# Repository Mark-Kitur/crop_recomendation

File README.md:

**Smart Crop Recommendation System**

link to the video: https://youtu.be/nVsl1SV6peM?si=QAl62YudmvHhIrHM

**Overview**

This project implements a Crop Recommendation System that suggests the most suitable crop to grow based on soil nutrients and environmental conditions. It combines Machine Learning (ML) with IoT (ESP8266 microcontroller) to support precision agriculture.
The workflow:
Collected and preprocessed agricultural data (soil nutrients & climate).
Trained a Random Forest Classifier model to recommend crops.
 Built a Flask web application for user-friendly crop prediction and farming advice.
 Converted the trained ML model to C code (micromlgen) and deployed it on an ESP8266 NodeMCU microcontroller.

Dataset
The dataset includes soil and environmental features:
N: Nitrogen content ratio in soil
P: Phosphorus content ratio in soil
K: Potassium content ratio in soil
Temperature: in °C
Humidity: in %
pH: Soil acidity/alkalinity
Rainfall: in mm

Tech Stack

Machine Learning: Random Forest Classifier (scikit-learn)

Web Framework: Ruby and Flask

Frontend: HTML, CSS (simple UI for predictions)

Microcontroller: ESP8266 (NodeMCU)

TinyML Library: micromlgen for C model export

Flask Web App
The web app allows users to:
Input soil & environmental parameters.
Get the best crop recommendation.
Receive advice on optimizing conditions (nutrients, pH, rainfall, etc.).

**Ruby Backend With ONNX Runtime**
The second deployment path validates language-agnostic inference by converting the trained Random Forest model to ONNX format.

Key Steps

Export trained model from Python → ONNX

Load ONNX model in Ruby using onnxruntime gem

Run inference directly from Ruby backend code

Serve predictions to a lightweight Ruby-based web endpoint or CLI script

Purpose

Demonstrates cross-platform, cross-language model deployment

Makes the engine compatible with Ruby web stacks (e.g., Rails, Sinatra)

Confirms interoperability without retraining or rewriting ML code

Ruby Deployment Capabilities

The Ruby ONNX version can:

Accept soil parameters via a web form or API

Run fast inference locally using ONNX Runtime

Return the crop recommendation + condition improvement notes

**ESP8266 Deployment**
The trained Random Forest model was converted into C code.
Deployed on ESP8266 NodeMCU with:
DHT11 sensor for temperature & humidity.
LCD display to show predicted crop.
Random values (for testing) simulating N, P, K, pH, rainfall.
Feel free to fork, improve, or suggest enhancements. Together, let’s make farming smarter

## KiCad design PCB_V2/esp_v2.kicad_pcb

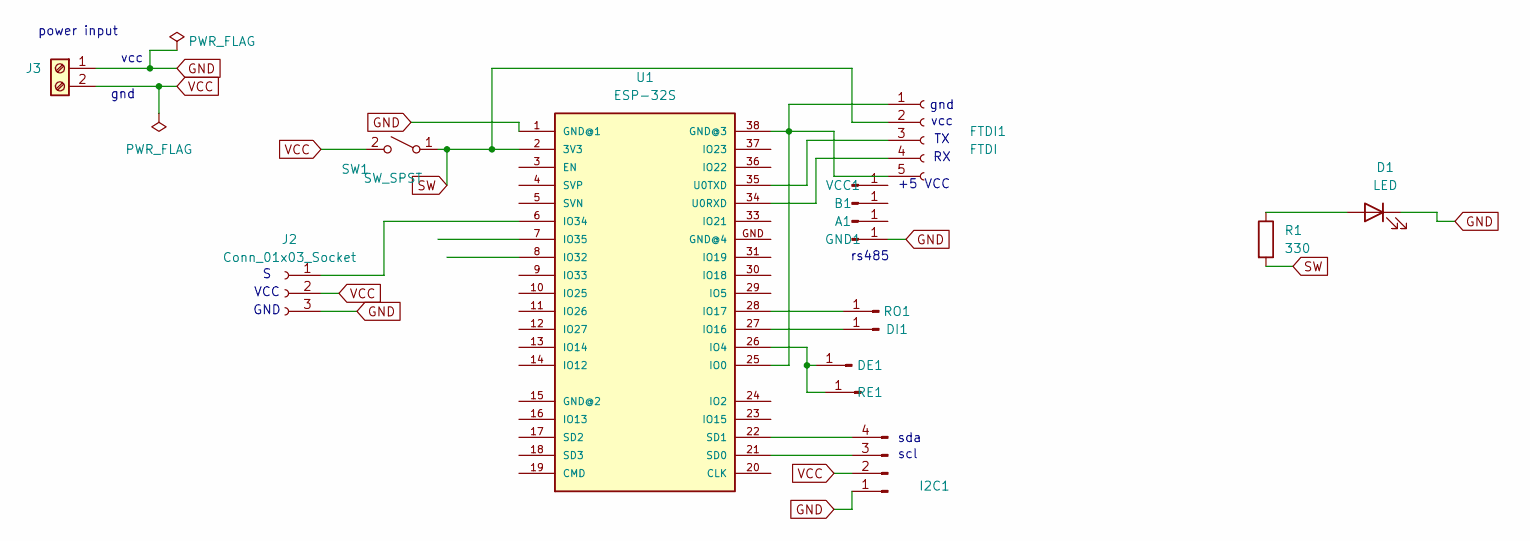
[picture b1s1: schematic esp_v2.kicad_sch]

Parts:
A1: Conn_01x01_Pin; PinHeader_1x01_P2.54mm_Vertical
B1: Conn_01x01_Pin; PinHeader_1x01_P2.54mm_Vertical
D1: LED; LED_D1.8mm_W3.3mm_H2.4mm
DE1: Conn_01x01_Pin; PinHeader_1x01_P2.54mm_Vertical
DI1: DI; PinHeader_1x01_P2.54mm_Vertical
FTDI1: FTDI; PinSocket_1x05_P2.54mm_Vertical
GND1: Conn_01x01_Pin; PinHeader_1x01_P2.54mm_Vertical
I2C1: Conn_01x04_Pin; PinHeader_1x04_P2.54mm_Vertical
J2: Conn_01x03_Socket; PinSocket_1x03_P2.54mm_Vertical
J3: Screw_Terminal_01x02; TerminalBlock_4Ucon_1x02_P3.50mm_Vertical
R1: 330; R_0815_2038Metric_Pad1.20x4.05mm_HandSolder
RE1: Conn_01x01_Pin; PinHeader_1x01_P2.54mm_Vertical
RO1: Conn_01x01_Pin; PinHeader_1x01_P2.54mm_Vertical
SW1: SW_SPST; SW_DIP_SPSTx01_Slide_6.7x4.1mm_W8.61mm_P2.54mm_LowProfile
U1: ESP-32S
VCC1: Conn_01x01_Pin; PinHeader_1x01_P2.54mm_Vertical

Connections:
GND: D1.1 (K), GND1.1, I2C1.1, J2.3, J3.1, U1.1 (GND@1)
unnamed: D1.2 (A), R1.1
unnamed: DE1.1, RE1.1, U1.26 (IO4)
unnamed: DI1.1, U1.27 (IO16)
unnamed: FTDI1.1, FTDI1.5, U1.25 (IO0), U1.38 (GND@3)
unnamed: FTDI1.3, U1.35 (U0TXD)
unnamed: FTDI1.4, U1.34 (U0RXD)
unnamed: I2C1.3, U1.21 (SD0)
unnamed: I2C1.4, U1.22 (SD1)
unnamed: J2.1, U1.6 (IO34)
unnamed: RO1.1, U1.28 (IO17)
SW: FTDI1.2, R1.2, SW1.1 (A), U1.2 (3V3)
VCC: I2C1.2, J2.2, J3.2, SW1.2 (B)

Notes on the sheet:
sda
+5 VCC
VCC
vcc
scl
gnd
power input
gnd
rs485
GND

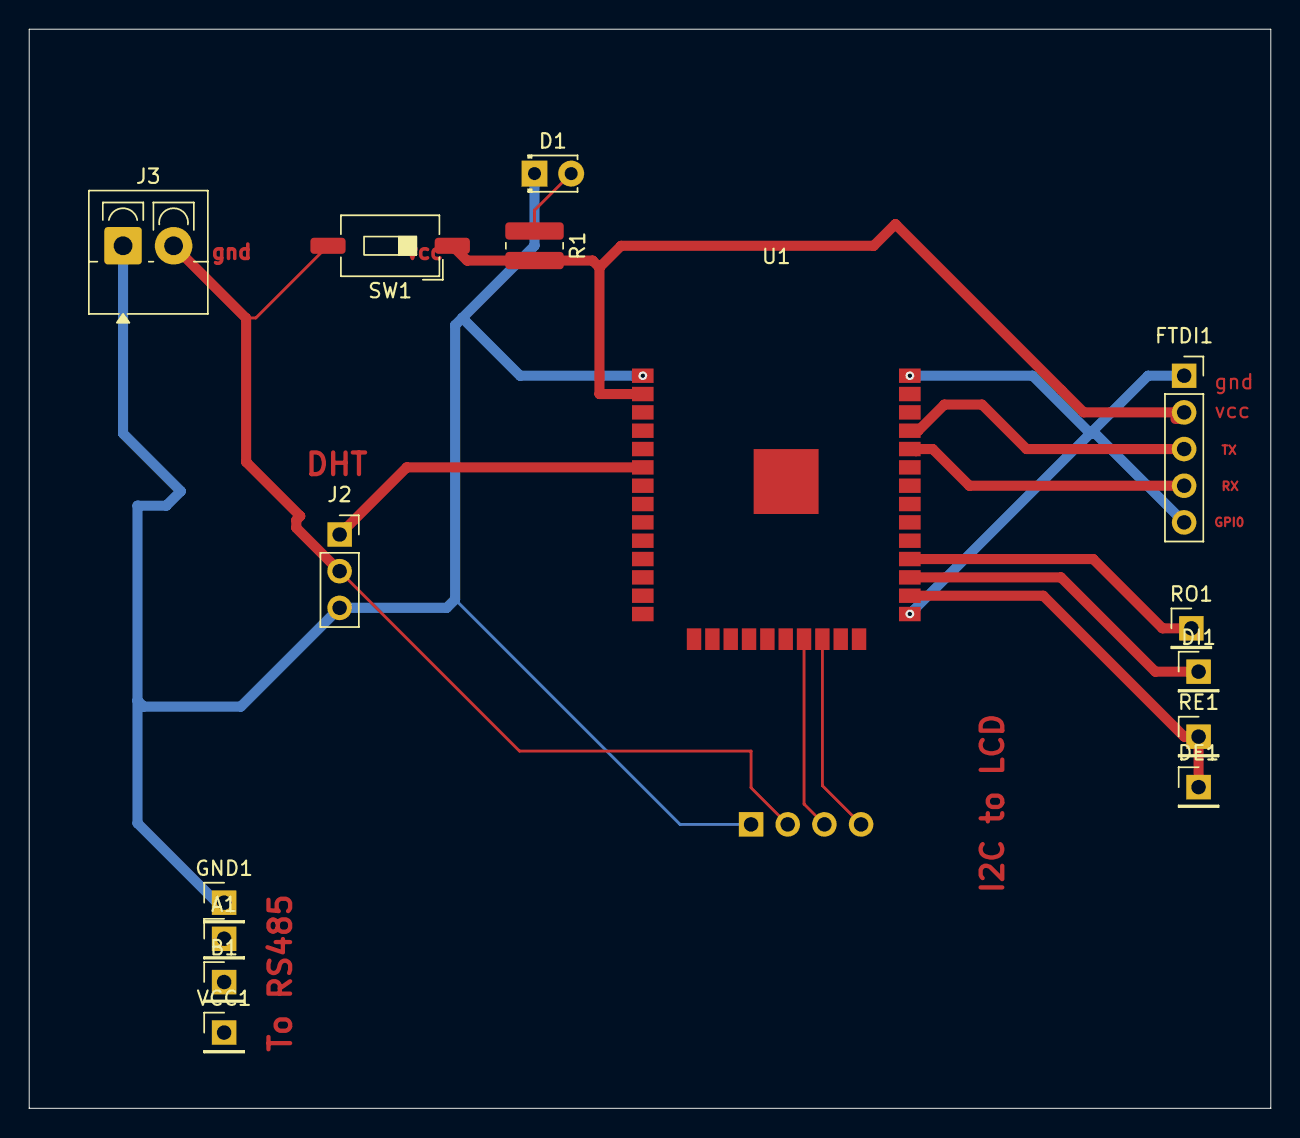
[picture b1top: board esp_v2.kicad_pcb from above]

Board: 2 copper layers, 86.0 x 74.8 mm, 16 parts (1 on the bottom side), 13 nets.

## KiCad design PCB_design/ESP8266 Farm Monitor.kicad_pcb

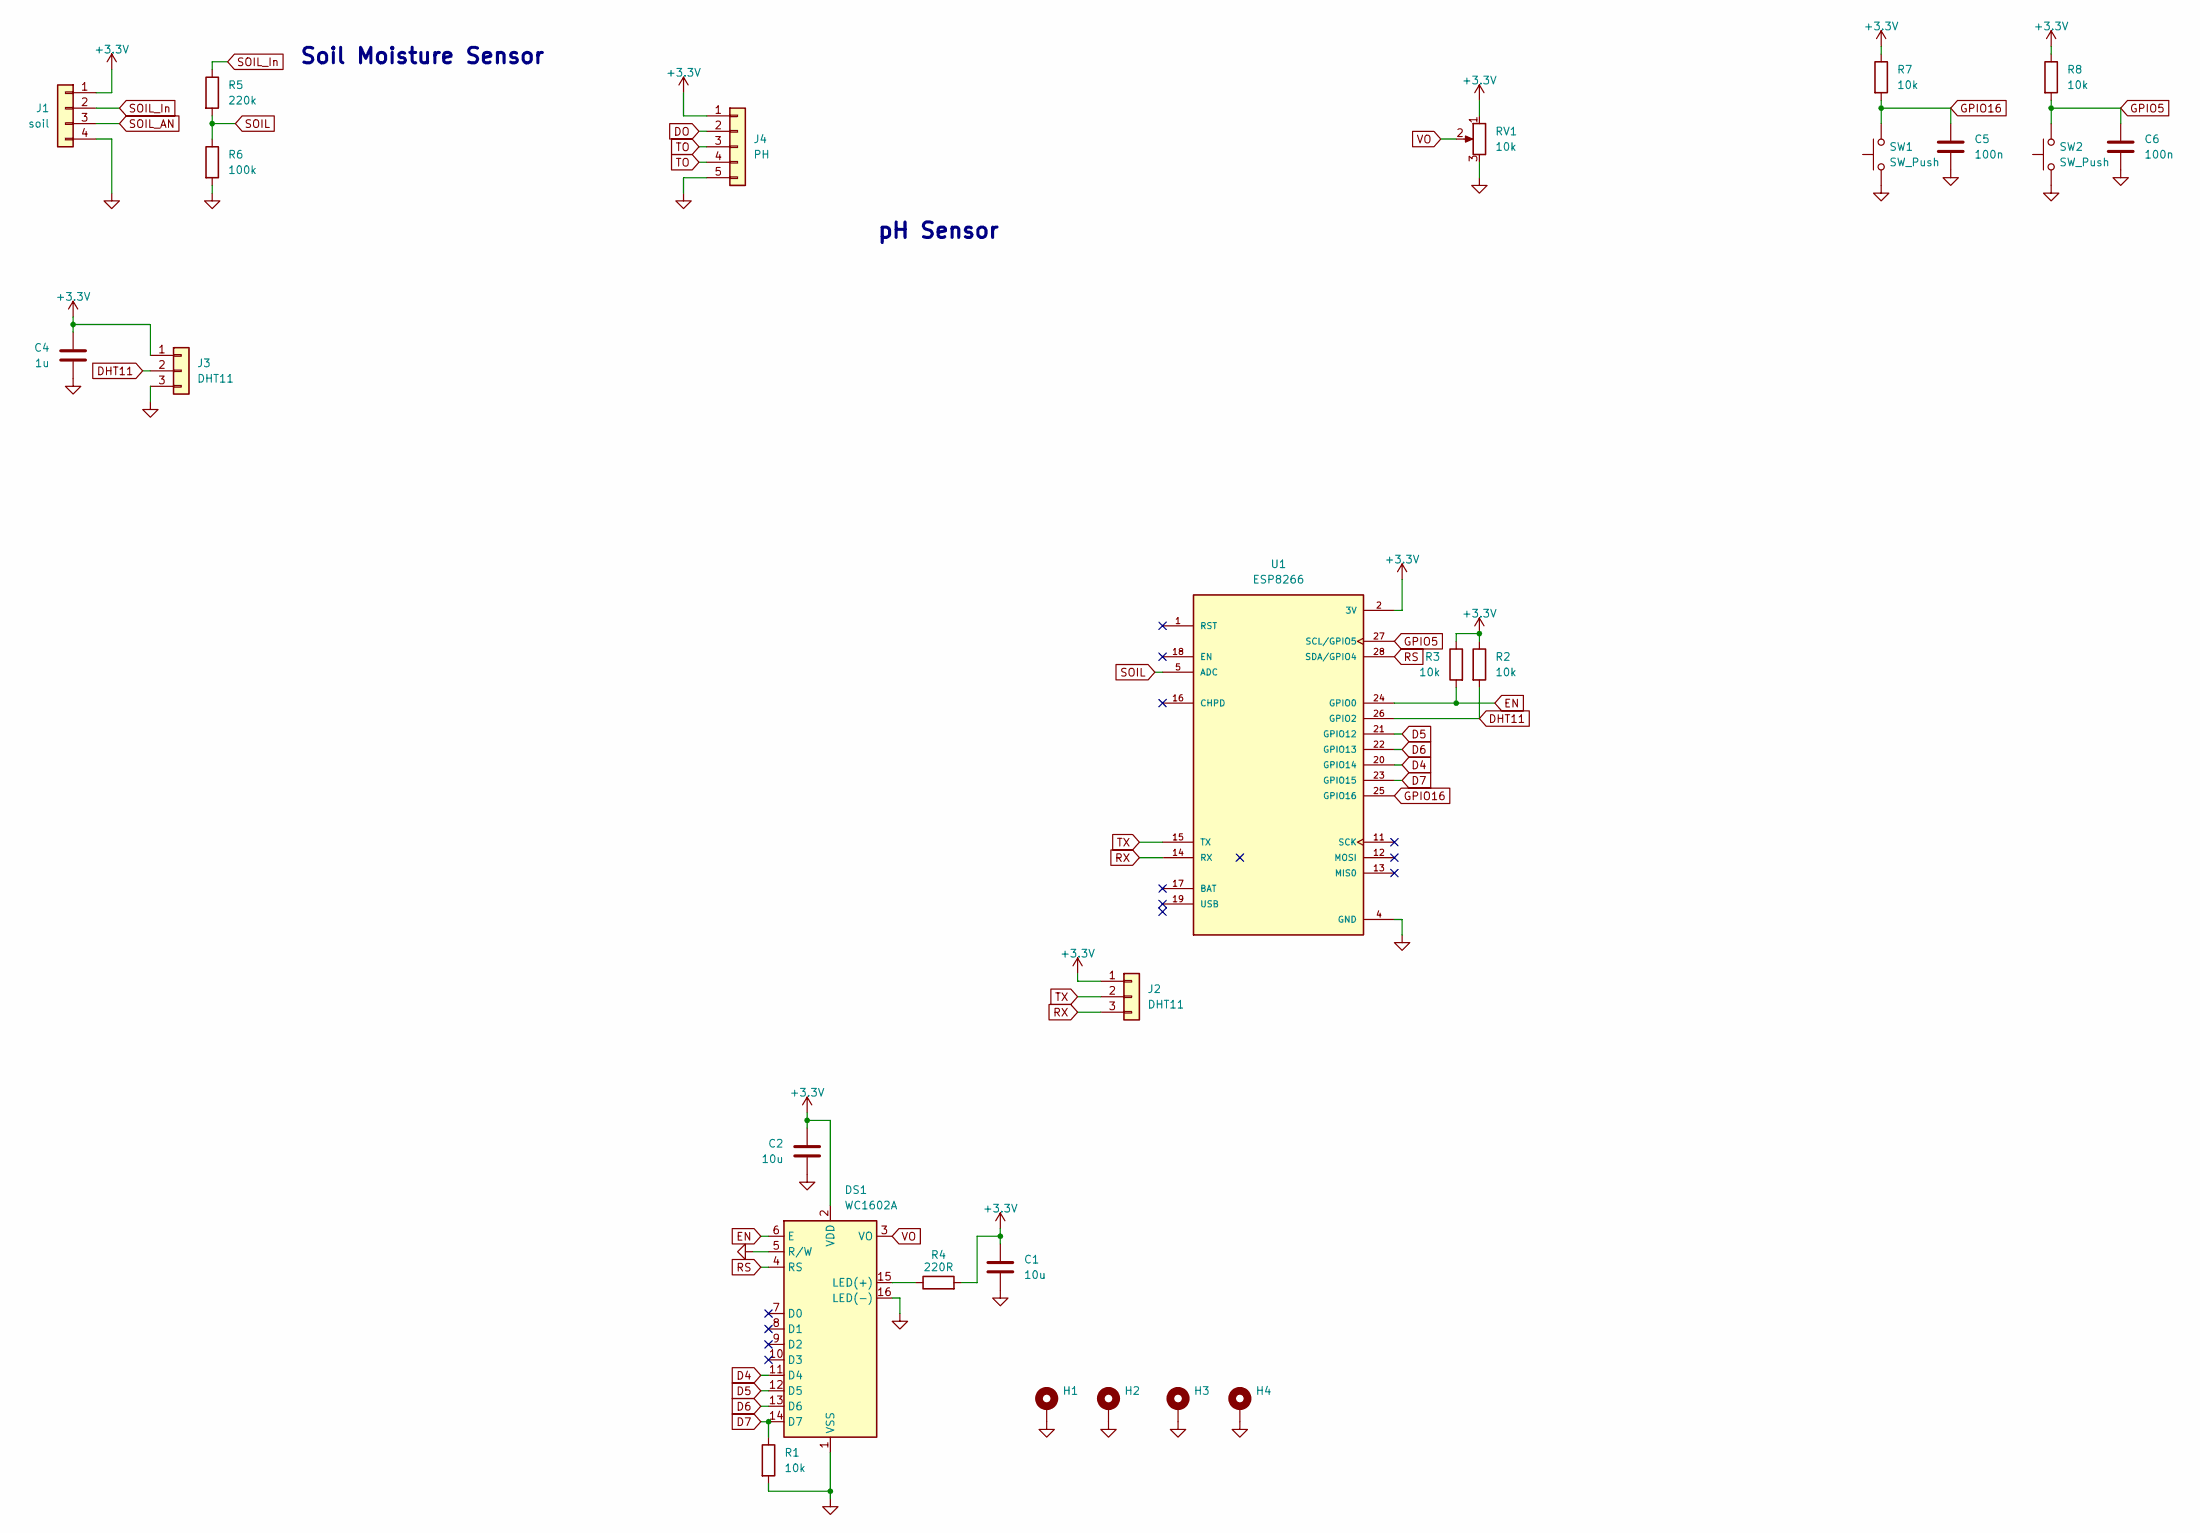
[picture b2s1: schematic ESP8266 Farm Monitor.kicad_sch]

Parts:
C1, C2: 10u; C_0603_1608Metric
C4: 1u; C_0603_1608Metric
C5, C6: 100n; C_0603_1608Metric
DS1: WC1602A
H1, H2, H3, H4: MountingHole_Pad; MountingHole_2.2mm_M2_Pad
J1: soil; PinHeader_1x04_P2.54mm_Vertical
J2, J3: DHT11; PinHeader_1x03_P2.54mm_Vertical
J4: PH; PinHeader_1x05_P2.54mm_Vertical
R1, R2, R3, R7, R8: 10k; R_0402_1005Metric
R4: 220R; R_Axial_DIN0204_L3.6mm_D1.6mm_P5.08mm_Horizontal
R5: 220k; R_0402_1005Metric
R6: 100k; R_0402_1005Metric
RV1: 10k; TRIM_3362P-1-103
SW1, SW2: SW_Push; SW_SKRPACE010
U1: ESP8266; XCVR_ESP8266

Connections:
+3.3V: C1.1, C2.1, C4.1, DS1.2 (VDD), J1.1, J2.1, J3.1, J4.1, R2.1, R3.1, R4.2, R7.1, R8.1, RV1.1, U1.2 (3V)
D4: DS1.11 (D4), U1.20 (GPIO14)
D5: DS1.12 (D5), U1.21 (GPIO12)
D6: DS1.13 (D6), U1.22 (GPIO13)
D7: DS1.14 (D7), R1.1, U1.23 (GPIO15)
DHT11: J3.2, R2.2, U1.26 (GPIO2)
DO: J4.2
EN: DS1.6 (E), R3.2, U1.24 (GPIO0)
GND: C1.2, C2.2, C4.2, C5.2, C6.2, DS1.1 (VSS), DS1.5 (R/W), DS1.16 (LED(-)), H1.1, H2.1, H3.1, H4.1, J1.4, J3.3, J4.5, R1.2, R6.2, RV1.3, SW1.1, SW2.1, U1.4 (GND)
GPIO5: C6.1, R8.2, SW2.2, U1.27 (SCL/GPIO5)
GPIO16: C5.1, R7.2, SW1.2, U1.25 (GPIO16)
unnamed: DS1.15 (LED(+)), R4.1
RS: DS1.4 (RS), U1.28 (SDA/GPIO4)
RX: J2.3, U1.14 (RX)
SOIL: R5.2, R6.1, U1.5 (ADC)
SOIL_AN: J1.3
SOIL_In: J1.2, R5.1
TO: J4.3, J4.4
TX: J2.2, U1.15 (TX)
VO: DS1.3 (VO), RV1.2

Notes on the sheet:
Soil Moisture Sensor
pH Sensor

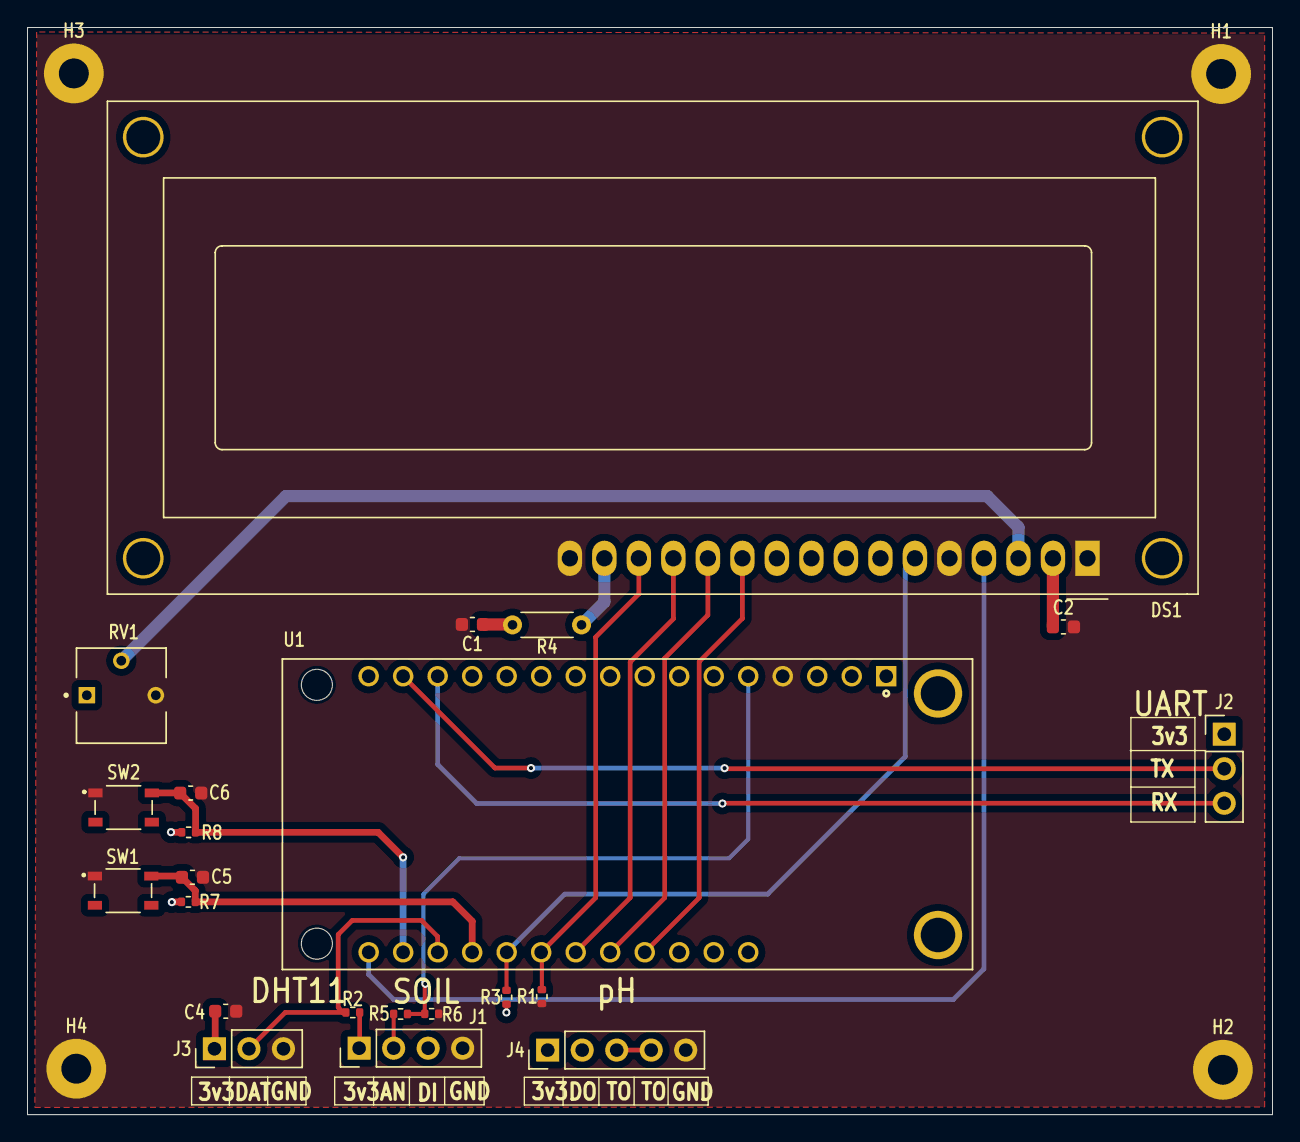
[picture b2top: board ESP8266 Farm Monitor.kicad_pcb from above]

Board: 2 copper layers, 91.6 x 80.0 mm, 26 parts (0 on the bottom side), 18 nets.

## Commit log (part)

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2025-05-01 first submission
2025-05-01 Creation of Requirements
2025-05-01 remove two sklearn
2025-05-01 use joblib
2025-05-01 using proper loading
2025-05-01 change label
2025-05-08 Addicting recommendation option to prediction
2025-09-24 Made use of the try catch method to catch errors as a result of wrong user input.
2025-09-24 Included the flash() in the html files for a user to be notified when they have provided invalid input. (Input that isn't an integer or a float in this case)
2025-09-24 correction niutrents quantities
2025-09-24 words corrections
2025-09-25 Adding ESP8266 for IOT
2025-09-25 deleting rough files
2025-09-25 remove some comments
2025-10-03 justo see app
2025-10-03 Backend, done - Ombachi
2025-10-04 editted backend
2025-10-04 add oonx model
2025-10-04 Integrated the backend with the ML model via onnx
2025-10-05 add button
2025-10-06 Add files via upload
    An overview of the casing
2025-10-06 Base frontend done - Ombachi
2025-10-06 include esp to flask
2025-10-07 styled frontend, auth still needs work
2025-10-08 Auth is sorted-manual encoding
2025-10-08 Finalized development
2025-10-08 Finalized development 2.0
2025-11-30 adding edge impluse model
2026-02-08 Fix title formatting in README.md
    Updated project title formatting in README.
2026-02-08 Expand README with Ruby and ONNX deployment info
    Added Ruby backend deployment details and ONNX model integration steps.
2026-02-20 startig computer vison
2026-03-04 adding PCB design
2026-03-30 starting knn aiming to recommend based on farmer's choice
2026-04-12 adding vesrion of PCB design by Mark-Kitur
2026-04-12 updating .gitignore
2026-04-13 doing EDA for the new algorithim
2026-04-16 corected the VCC for 7in1
2026-04-19 expanded tracks' width
2026-04-21 After our first etching we reiliaze pins were too small . SO we had toenlearge them.
2026-04-26 intergrating 7 in 1 soil sensor
2026-04-26 7 in 1 sensor is now fully functional and working with the model
2026-04-29 validating pCB wrt to ftdi promgrammer
2026-04-29 adding vias to mke back connections
2026-05-16 correction on I2C for the lcd
2026-06-11 added power button
